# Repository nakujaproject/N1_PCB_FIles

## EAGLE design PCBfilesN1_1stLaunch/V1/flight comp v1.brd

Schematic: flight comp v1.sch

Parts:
C1, C2: C2,5-3; C2.5-3
IC1: 7805TV; TO220V
SG1: B/C11L
SV1: MA03-1
U1: GY-521MPU6050; GY-521
U$1: ESP32DEVKITC; ESP32-DEVKITC
U$2: MICROSDADAPTER
U$3: BMP180
U$4: DBCONN-1X2

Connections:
3V3: U$1.1 (3V3), U$3.VIN
5V: C2.1, IC1.3 (VO), SV1.2, U1.VCC, U$1.19 (5V), U$2.VCC1 (VCC)
BUZZER: SG1.1, U$1.15 (IO13)
CS: U$1.29 (IO5), U$2.CS1 (CS)
GND: C1.2, C2.2, IC1.2 (GND), SG1.2, SV1.3, U1.GND, U$1.38 (GND), U$2.GND1 (GND), U$3.GND, U$4.P0
MISO: U$1.31 (IO19), U$2.MISO1 (MISO)
MOSI: U$1.37 (IO23), U$2.MOSI1 (MOSI)
unnamed: C1.1, IC1.1 (VI), U$4.P1
PWM: SV1.1, U$1.23 (IO15)
SCK: U$1.30 (IO18), U$2.SCK1 (SCK)
SCL: U1.SCL, U$1.12 (IO14), U$3.SCL
SDA: U1.SDA, U$1.13 (IO12), U$3.SDA

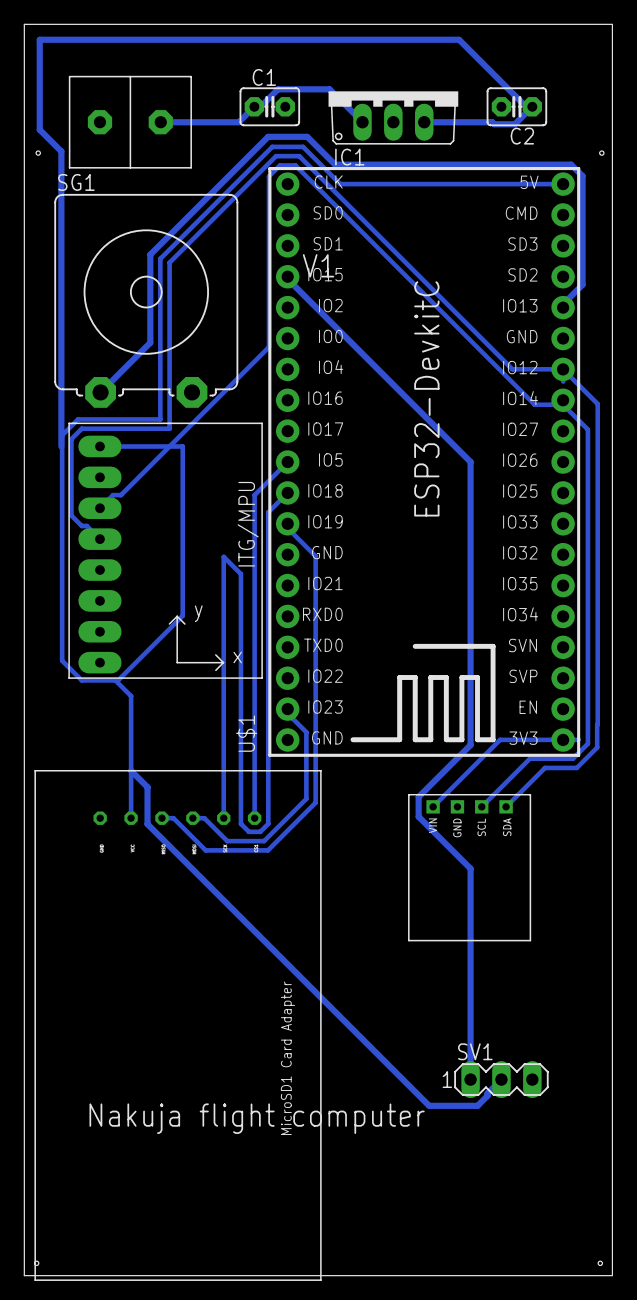
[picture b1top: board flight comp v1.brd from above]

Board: 2 copper layers, 48.4 x 102.9 mm, 10 parts (0 on the bottom side), 12 nets.

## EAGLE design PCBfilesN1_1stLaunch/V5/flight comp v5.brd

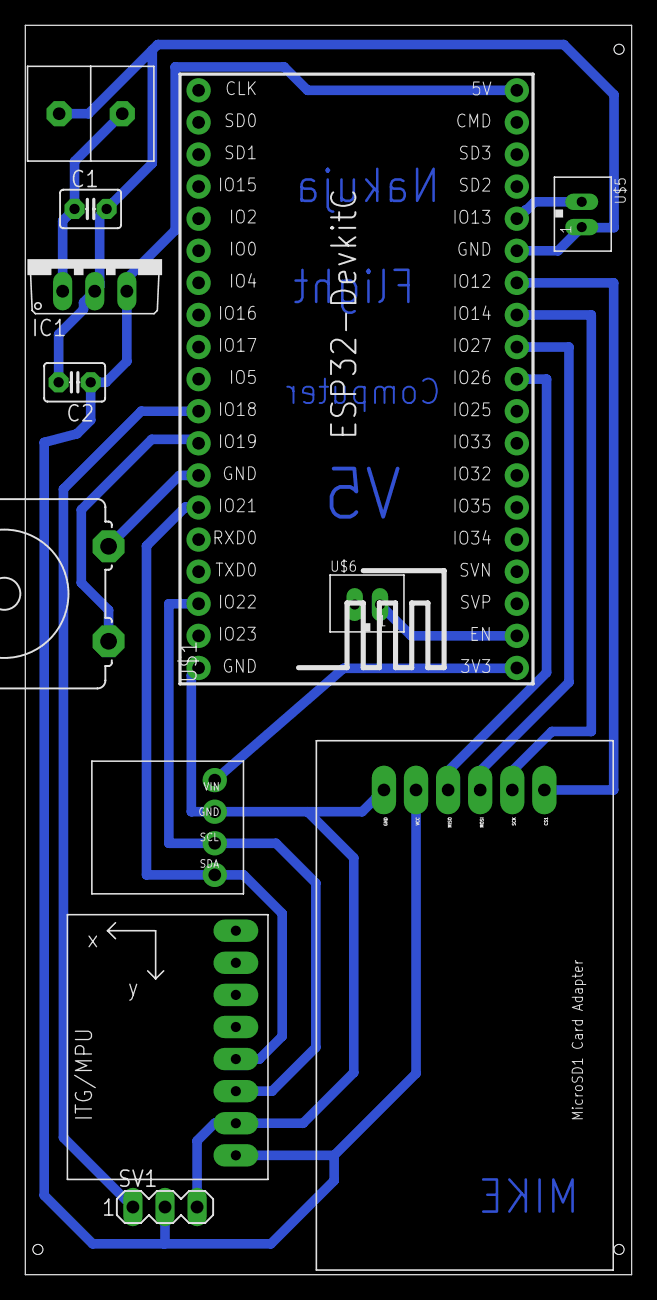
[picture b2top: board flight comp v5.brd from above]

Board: 2 copper layers, 48.0 x 98.9 mm, 12 parts (0 on the bottom side), 14 nets.

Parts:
C1, C2: C2.5-3
IC1: 7805TV; TO220V
SG1: B/C11L
SV1: MA03-1
U1: GY-521MPU6050; GY-521
U$1: ESP32DEVKITC; ESP32-DEVKITC
U$2: MICROSDADAPTER
U$3: BMP180
U$4: DBCONN-1X2
U$5, U$6: JST-PH_2-PIN_HEADER; JST_B2B-PH_HEADER

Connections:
3V3: U$1.1, U$3.VIN
5V: C2.1, IC1.3, SV1.2, U1.VCC, U$1.19, U$2.VCC1
BUZZER: SG1.1, U$1.31
CS: U$1.13, U$2.CS1
EN: U$1.2, U$6.P1
GND: C1.2, C2.2, IC1.2, SG1.2, SV1.3, U1.GND, U$1.14, U$1.32, U$1.38, U$2.GND1, U$3.GND, U$4.P0, U$5.P1, U$6.P2
MISO: U$1.10, U$2.MISO1
MOSI: U$1.11, U$2.MOSI1
unnamed: C1.1, IC1.1, U$4.P1
PWM: SV1.1, U$1.30
RST: U$1.15, U$5.P2
SCK: U$1.12, U$2.SCK1
SCL: U1.SCL, U$1.36, U$3.SCL
SDA: U1.SDA, U$1.33, U$3.SDA

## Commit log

2021-04-27 PCB files versions
2021-06-08 Rearranging
2021-06-08 Improved N1 circuit
2021-06-08 Adding schematic in json form
2021-06-18 Added PCB design

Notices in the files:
parts and their libraries:
SparkFun-Aesthetics: Licensing: Creative Commons ShareAlike 4.0 International - https://creativecommons.org/licenses/by-sa/4.0
